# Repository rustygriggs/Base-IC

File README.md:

# The various pieces necesary for all of Base-IC

- **BaseStation**
-- **apiwebapp** Django API manages the database of all peripherals as well as the IFTTT workflows that are attached to each peripheral and service. This is where the iOS and Android app will connect to manage and interace with the home automation system.
-- **apiworker** Worker that listens to Rabbit MQ and calls the applicable API endpoints when packets are received.
-- **zigbeeworker** Worker that listens to a serial port (with Zigbee attached) and translates any packets from the zigbee network and places them on Rabbit MQ to be sent to the API Worker.
- **HomeAutomationModule** Eagle layout for a module with a built in Arduino.
- **HomeAutomationModuleV2** Eagle layout for a module that attaches to an Arudino Nano.
- **LEDPeripheral** PlatformIO (Arduino) code that houses the BaseIC SDK for Arduino development.
- **OldBaseStation** Some experiments that didn't pan out.

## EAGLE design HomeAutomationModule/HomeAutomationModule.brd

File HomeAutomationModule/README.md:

# Home automation module

Combines DigiMesh 2.4 module with an arduino compatible board.

Using the library file for xbee found here (https://www.diymodules.org/download/eagle-libs/usr/0000002762/conv/xbee.lbr)

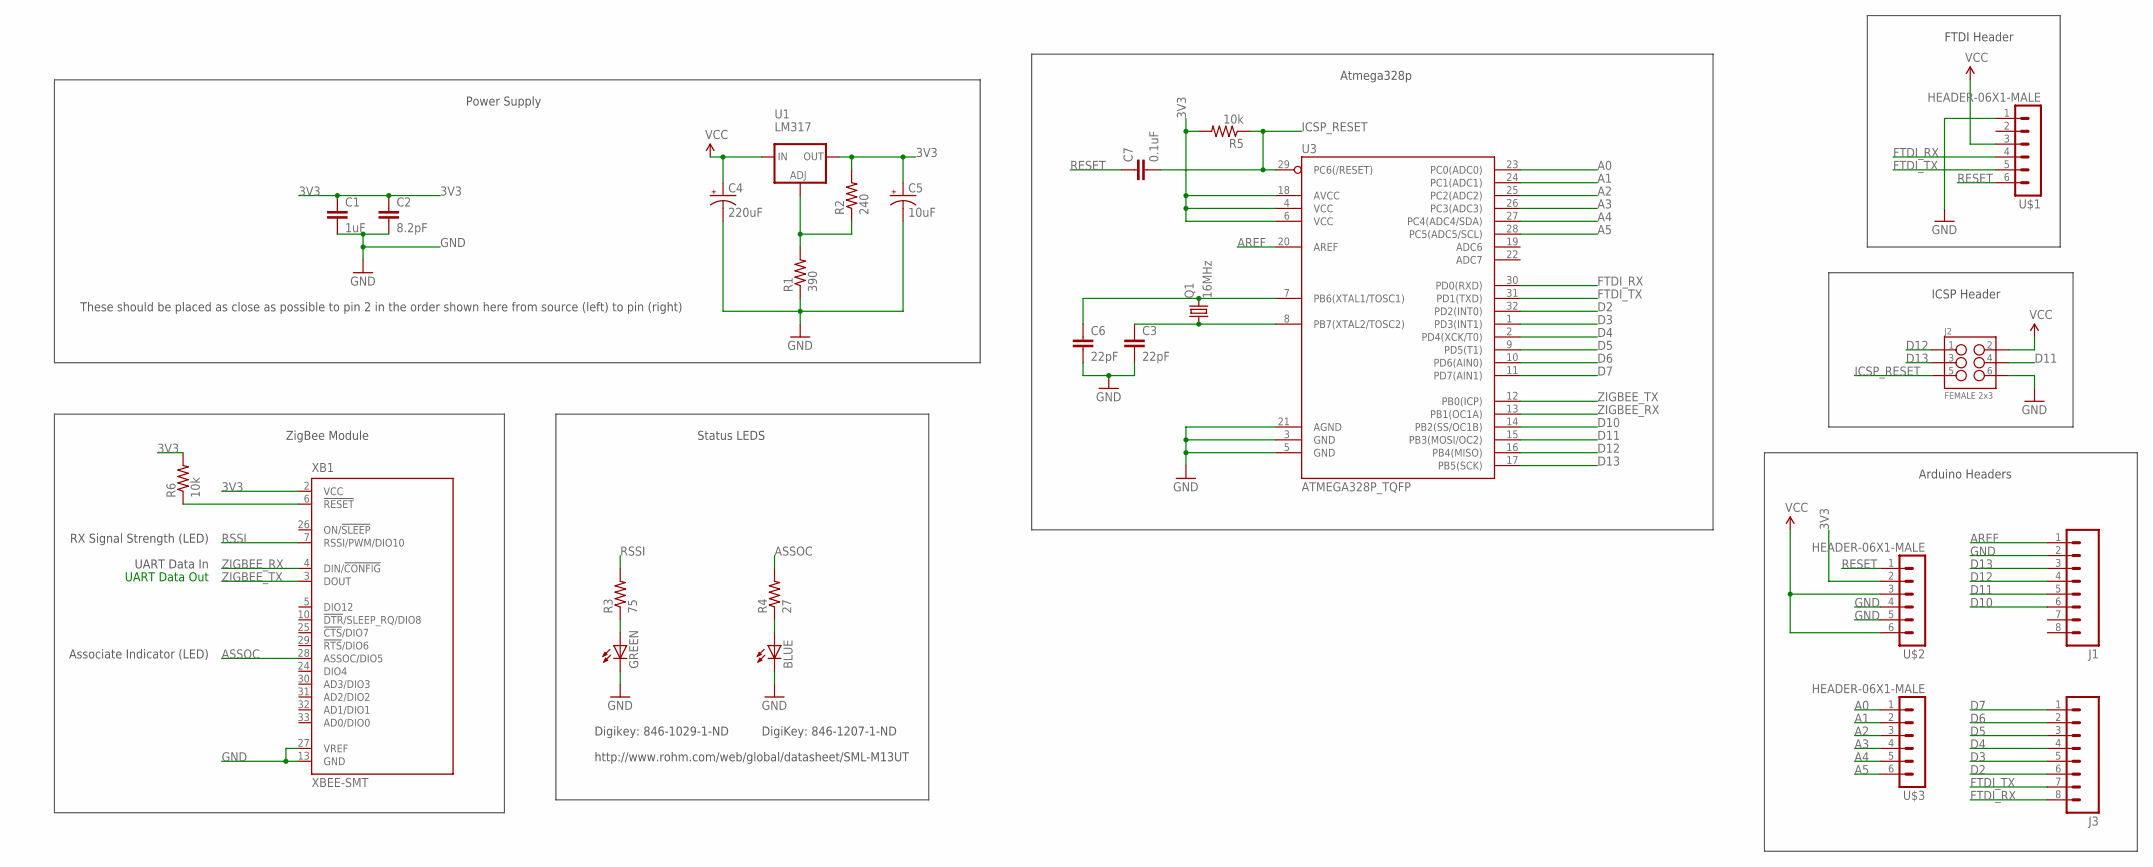
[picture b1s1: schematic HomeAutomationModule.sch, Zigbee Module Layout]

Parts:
BLUE: LEDCHIP-LED0805; CHIP-LED0805
C1: 1uF; 0805-CAP
C2: 8.2pF; 0805-CAP
C3, C6: 22pF; 0805-CAP
C4: 220uF; CPOL-RADIAL-10UF-25V
C5: 10uF; CPOL-RADIAL-10UF-25V
C7: 0.1uF; 0805-CAP
GREEN: LEDCHIP-LED0805; CHIP-LED0805
J1, J3: M08; 1X08_ROUND
J2: FEMALE 2x3; 2X3
Q1: 16MHz; HC49/S
R1: 390; 0805
R2: 240; 0805
R3: 75; 0805
R4: 27; 0805
R5, R6: 10k; 0805
U1: LM317; SOT223
U3: ATMEGA328P_TQFP; TQFP32-08
U$1, U$2, U$3: HEADER-06X1-MALE; 06X1-PTH
XB1: XBEE-SMT

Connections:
3V3: C1.1, C2.1, C5.1 (+), R2.2, R5.2, R6.2, U1.2 (OUT), U3.4 (VCC), U3.6 (VCC), U3.18 (AVCC), U$2.2, XB1.2 (VCC)
A0: U3.23 (PC0(ADC0)), U$3.1
A1: U3.24 (PC1(ADC1)), U$3.2
A2: U3.25 (PC2(ADC2)), U$3.3
A3: U3.26 (PC3(ADC3)), U$3.4
A4: U3.27 (PC4(ADC4/SDA)), U$3.5
A5: U3.28 (PC5(ADC5/SCL)), U$3.6
AREF: J1.1, U3.20 (AREF)
ASSOC: R4.2, XB1.28 (ASSOC/DIO5)
D2: J3.6, U3.32 (PD2(INT0))
D3: J3.5, U3.1 (PD3(INT1))
D4: J3.4, U3.2 (PD4(XCK/T0))
D5: J3.3, U3.9 (PD5(T1))
D6: J3.2, U3.10 (PD6(AIN0))
D7: J3.1, U3.11 (PD7(AIN1))
D10: J1.6, U3.14 (PB2(SS/OC1B))
D11: J1.5, J2.4, U3.15 (PB3(MOSI/OC2))
D12: J1.4, J2.1, U3.16 (PB4(MISO))
D13: J1.3, J2.3, U3.17 (PB5(SCK))
FTDI_RX: J3.8, U3.30 (PD0(RXD)), U$1.4
FTDI_TX: J3.7, U3.31 (PD1(TXD)), U$1.5
GND: BLUE.C, C1.2, C2.2, C3.2, C4.2 (-), C5.2 (-), C6.2, GREEN.C, J1.2, J2.6, R1.1, U3.3 (GND), U3.5 (GND), U3.21 (AGND), U$1.1, U$2.4, U$2.5, XB1.13 (GND), XB1.27 (VREF)
ICSP_RESET: C7.2, J2.5, R5.1, U3.29 (PC6(/RESET))
unnamed: BLUE.A, R4.1
unnamed: R6.1, XB1.6 (!RESET)
unnamed: C6.1, Q1.2, U3.7 (PB6(XTAL1/TOSC1))
unnamed: C3.1, Q1.1, U3.8 (PB7(XTAL2/TOSC2))
unnamed: R1.2, R2.1, U1.1 (ADJ)
unnamed: GREEN.A, R3.1
RESET: C7.1, U$1.6, U$2.1
RSSI: R3.2, XB1.7 (RSSI/PWM/DIO10)
VCC: C4.1 (+), J2.2, U1.3 (IN), U$1.3, U$2.3, U$2.6
ZIGBEE_RX: U3.13 (PB1(OC1A)), XB1.4 (DIN/!CONFIG)
ZIGBEE_TX: U3.12 (PB0(ICP)), XB1.3 (DOUT)

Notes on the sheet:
Associate Indicator (LED)
RX Signal Strength (LED)
UART Data In
UART Data Out
These should be placed as close as possible to pin 2 in the order shown here from source (left) to pin (right)
ZigBee Module
Power Supply
DigiKey: 846-1207-1-ND
Digikey: 846-1029-1-ND
http://www.rohm.com/web/global/datasheet/SML-M13UT
Status LEDS
ICSP Header
FTDI Header
Arduino Headers
Atmega328p

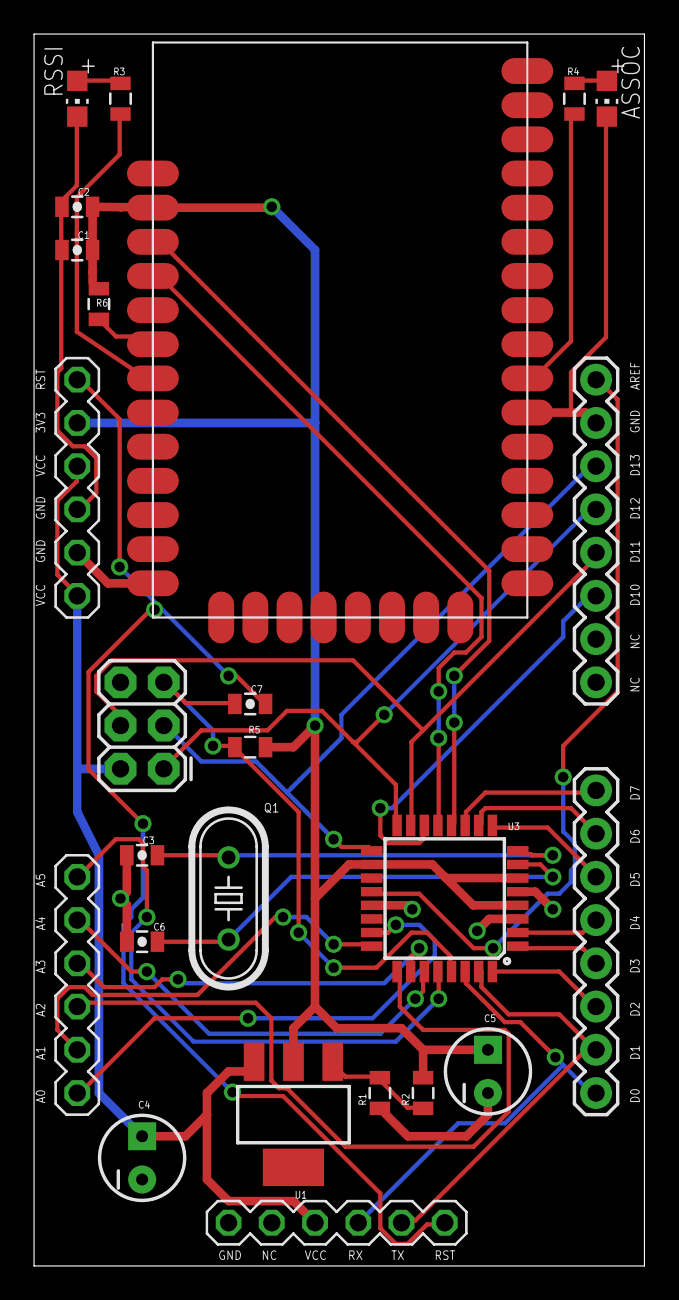
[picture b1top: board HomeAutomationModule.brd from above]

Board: 2 copper layers, 35.9 x 72.4 mm, 25 parts (0 on the bottom side), 34 nets.

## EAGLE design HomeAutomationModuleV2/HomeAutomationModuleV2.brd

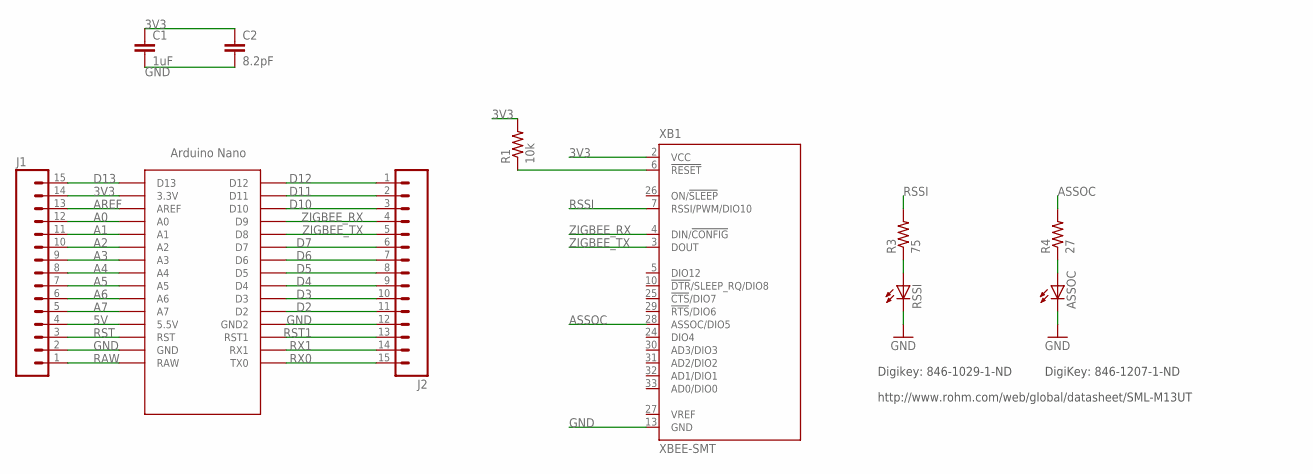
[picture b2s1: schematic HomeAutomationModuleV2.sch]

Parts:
ASSOC: LEDCHIP-LED0805; CHIP-LED0805
C1: 1uF; 0805-CAP
C2: 8.2pF; 0805-CAP
J1, J2: M15; 1X15
R1: 10k; 0805
R3: 75; 0805
R4: 27; 0805
RSSI: LEDCHIP-LED0805; CHIP-LED0805
U$1: NANO
XB1: XBEE-SMT

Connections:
3V3: C1.1, C2.1, J1.14, R1.2, U$1.3.3V, XB1.2 (VCC)
5V: J1.4, U$1.5V (5.5V)
A0: J1.12, U$1.A0
A1: J1.11, U$1.A1
A2: J1.10, U$1.A2
A3: J1.9, U$1.A3
A4: J1.8, U$1.A4
A5: J1.7, U$1.A5
A6: J1.6, U$1.A6
A7: J1.5, U$1.A7
AREF: J1.13, U$1.AREF
ASSOC: R4.2, XB1.28 (ASSOC/DIO5)
D2: J2.11, U$1.D2
D3: J2.10, U$1.D3
D4: J2.9, U$1.D4
D5: J2.8, U$1.D5
D6: J2.7, U$1.D6
D7: J2.6, U$1.D7
D10: J2.3, U$1.D10
D11: J2.2, U$1.D11
D12: J2.1, U$1.D12
D13: J1.15, U$1.D13
GND: ASSOC.C, C1.2, C2.2, J1.2, J2.12, RSSI.C, U$1.GND, U$1.GND1 (GND2), XB1.13 (GND)
unnamed: ASSOC.A, R4.1
unnamed: R1.1, XB1.6 (!RESET)
unnamed: R3.1, RSSI.A
RAW: J1.1, U$1.RAW
RSSI: R3.2, XB1.7 (RSSI/PWM/DIO10)
RST: J1.3, U$1.RST
RST1: J2.13, U$1.RST1
RX0: J2.15, U$1.TX0
RX1: J2.14, U$1.RX1
ZIGBEE_RX: J2.4, U$1.D9, XB1.4 (DIN/!CONFIG)
ZIGBEE_TX: J2.5, U$1.D8, XB1.3 (DOUT)

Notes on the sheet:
DigiKey: 846-1207-1-ND
Digikey: 846-1029-1-ND
http://www.rohm.com/web/global/datasheet/SML-M13UT

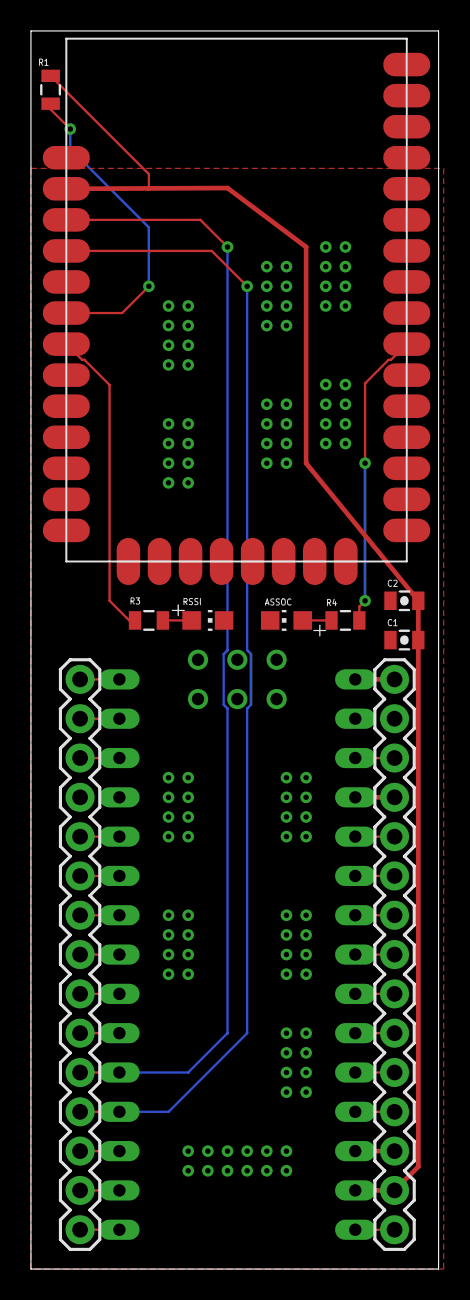
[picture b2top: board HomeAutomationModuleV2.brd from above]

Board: 2 copper layers, 26.3 x 80.0 mm, 11 parts (0 on the bottom side), 34 nets.

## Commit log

2017-04-28 Added HomeAutomationModulePCBLayout.
2017-04-28 Updated HomeAutomationPCBLayout
2017-04-30 Update PCB Schematic.
2017-06-12 Added Base-IC-Server and updated module PCB layout.
2017-09-02 Added the actual code to the repo.
2017-09-02 Remove accidental sub-git module for HomeAutomationModule. Read README.md
2017-09-02 Remove more sub git modules that shouldn't have been sub git modules.
2017-09-02 Added the API Docs.
2017-09-10 Added workflows to the api web app. The web app also can publish messages via pika to RabbitMQ which are then received by the zigbee worker.
2017-09-10 Update zigbee serial and worker to parse data that they receive from the message queue and put it on the serial line.
2017-09-16 Updated requirements.
2017-09-16 Updated the api to accept the api process command which will receive all information from the api worker. The api can now create new peripherals when a peripehral tries to register itself.
2017-09-16 Corrected a spelling error.
2017-09-16 Redid the migrations to add extra information to the periperhal service table.
2017-09-17 Peripheral registration should be working now.
2017-09-18 Rename workflows to recipes.
2017-09-18 Updates.
2017-09-18 Rename to and from to input and output.
2017-09-18 Change Xbee to XbeeWithCallbacks. Allow the developer to attach a listener to the Xbee device and receive data whenever anything is addressed to that device.
2017-09-20 Begin working on ButtonPeripheral. Expand Arduino BaseIC library to allow sending an 8 byte int as hex.
2017-09-23 Added a script to start gunicorn.
2017-09-23 Added code to the protocol to send and receive commands. Simplified the views and removed those that are unnecessary now. Update button peripheral to send 1 and 2 corresponding to the two buttons.
2017-09-24 Began setting up the frontend webapp.
2017-09-24 Remove webpack-stats from repo.
2017-10-12 A few updates. Changed from MySQL to SQLite3.
2017-10-12 Changed the LED peripheral to use a micro rather than a nano.
2017-10-22 Change LED periperhal to a nano. APIWorker needs to use localhost on port 80 when connection to the api.
2017-10-23 Re-work the BaseIC sdk.
2017-10-24 Added bootstrap and got some web stylings.
2017-10-24 Export ActionPeripheral
2017-10-26 Note that everything is working right now
2017-10-26 everything is working with this commit
2017-11-16 Added button 4,5,6 to button peripheral. Changed apiwebapp to say peripherals since it is a list of peripherals.
2017-11-16 Correct URL for pi.
2017-11-16 Make the react app use peripherals rather than peripheral.
2017-11-16 Added the first working FancyLEDPeripheral.
2017-11-23 Updated fancy led. Added four relay device.
2017-11-30 Changed curtain peripheral to one motor
2017-11-30 Updated for range
2017-11-30 removed zigbee timeout
2017-11-30 Added manual service names to api.
2017-11-30 When a range input is selected it will pass through the value to the output_value.
2017-12-01 Started working on displaying recipes.
2017-12-01 Updated package.json
2017-12-01 Updated BaseIC SDK to send the service ID with the sendInt command. Changed the name of the button peripheral since it will only have 9 buttons.
2017-12-01 Can now view recipes and edit the service name, input value, and output value.
2017-12-02 Finished the recipe editor. Can now create new recipes, edit old recipes, and delete recipes.
2017-12-05 door and deadlock working together
2017-12-06 Thermostat finished. IR remote created and still in progress
2017-12-07 Updated recipe table and row
2017-12-07 A some updates.
2017-12-08 Working fancy led light.
2017-12-08 Models should cascade on delete.
2017-12-08 added checks for the door and deadlock to work in synch
2017-12-09 door and deadlock working correctly
2019-10-21 Bump django from 1.11.6 to 1.11.23 in /BaseStation
    Bumps [django](https://github.com/django/django) from 1.11.6 to 1.11.23.
    - [Release notes](https://github.com/django/django/releases)
    - [Commits](https://github.com/django/django/compare/1.11.6...1.11.23)
2020-02-11 Bump django from 1.11.6 to 1.11.28 in /BaseStation
    Bumps [django](https://github.com/django/django) from 1.11.6 to 1.11.28.
    - [Release notes](https://github.com/django/django/releases)
    - [Commits](https://github.com/django/django/compare/1.11.6...1.11.28)
2020-04-29 Bump jquery from 3.2.1 to 3.5.0 in /BaseStation/apiwebapp
    Bumps [jquery](https://github.com/jquery/jquery) from 3.2.1 to 3.5.0.
    - [Release notes](https://github.com/jquery/jquery/releases)
    - [Commits](https://github.com/jquery/jquery/compare/3.2.1...3.5.0)
2020-06-05 Bump django from 1.11.6 to 1.11.29 in /BaseStation
    Bumps [django](https://github.com/django/django) from 1.11.6 to 1.11.29.
    - [Release notes](https://github.com/django/django/releases)
    - [Commits](https://github.com/django/django/compare/1.11.6...1.11.29)
2021-01-04 Bump axios from 0.17.1 to 0.21.1 in /BaseStation/apiwebapp
    Bumps [axios](https://github.com/axios/axios) from 0.17.1 to 0.21.1.
    - [Release notes](https://github.com/axios/axios/releases)
    - [Changelog](https://github.com/axios/axios/blob/v0.21.1/CHANGELOG.md)
    - [Commits](https://github.com/axios/axios/compare/v0.17.1...v0.21.1)
2021-03-19 Bump djangorestframework from 3.7.1 to 3.11.2 in /BaseStation
    Bumps [djangorestframework](https://github.com/encode/django-rest-framework) from 3.7.1 to 3.11.2.
    - [Release notes](https://github.com/encode/django-rest-framework/releases)
    - [Commits](https://github.com/encode/django-rest-framework/compare/3.7.1...3.11.2)
2021-06-01 Bump urllib3 from 1.22 to 1.26.5 in /BaseStation
    Bumps [urllib3](https://github.com/urllib3/urllib3) from 1.22 to 1.26.5.
    - [Release notes](https://github.com/urllib3/urllib3/releases)
    - [Changelog](https://github.com/urllib3/urllib3/blob/main/CHANGES.rst)
    - [Commits](https://github.com/urllib3/urllib3/compare/1.22...1.26.5)
    ---
    updated-dependencies:
2021-06-10 Bump django from 1.11.6 to 2.2.24 in /BaseStation
    Bumps [django](https://github.com/django/django) from 1.11.6 to 2.2.24.
    - [Release notes](https://github.com/django/django/releases)
    - [Commits](https://github.com/django/django/compare/1.11.6...2.2.24)
    ---
    updated-dependencies:
    - dependency-name: django
2022-11-15 Bump loader-utils from 1.1.0 to 1.4.2 in /BaseStation/apiwebapp
    Bumps [loader-utils](https://github.com/webpack/loader-utils) from 1.1.0 to 1.4.2.
    - [Release notes](https://github.com/webpack/loader-utils/releases)
    - [Changelog](https://github.com/webpack/loader-utils/blob/v1.4.2/CHANGELOG.md)
    - [Commits](https://github.com/webpack/loader-utils/compare/v1.1.0...v1.4.2)
    ---
    updated-dependencies:
2022-12-08 Bump certifi from 2017.7.27.1 to 2022.12.7 in /BaseStation
    Bumps [certifi](https://github.com/certifi/python-certifi) from 2017.7.27.1 to 2022.12.7.
    - [Release notes](https://github.com/certifi/python-certifi/releases)
    - [Commits](https://github.com/certifi/python-certifi/compare/2017.07.27.1...2022.12.07)
    ---
    updated-dependencies:
    - dependency-name: certifi

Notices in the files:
parts and their libraries:
SparkFun-Capacitors: Licensing: Creative Commons ShareAlike 4.0 International - https://creativecommons.org/licenses/by-sa/4.0
